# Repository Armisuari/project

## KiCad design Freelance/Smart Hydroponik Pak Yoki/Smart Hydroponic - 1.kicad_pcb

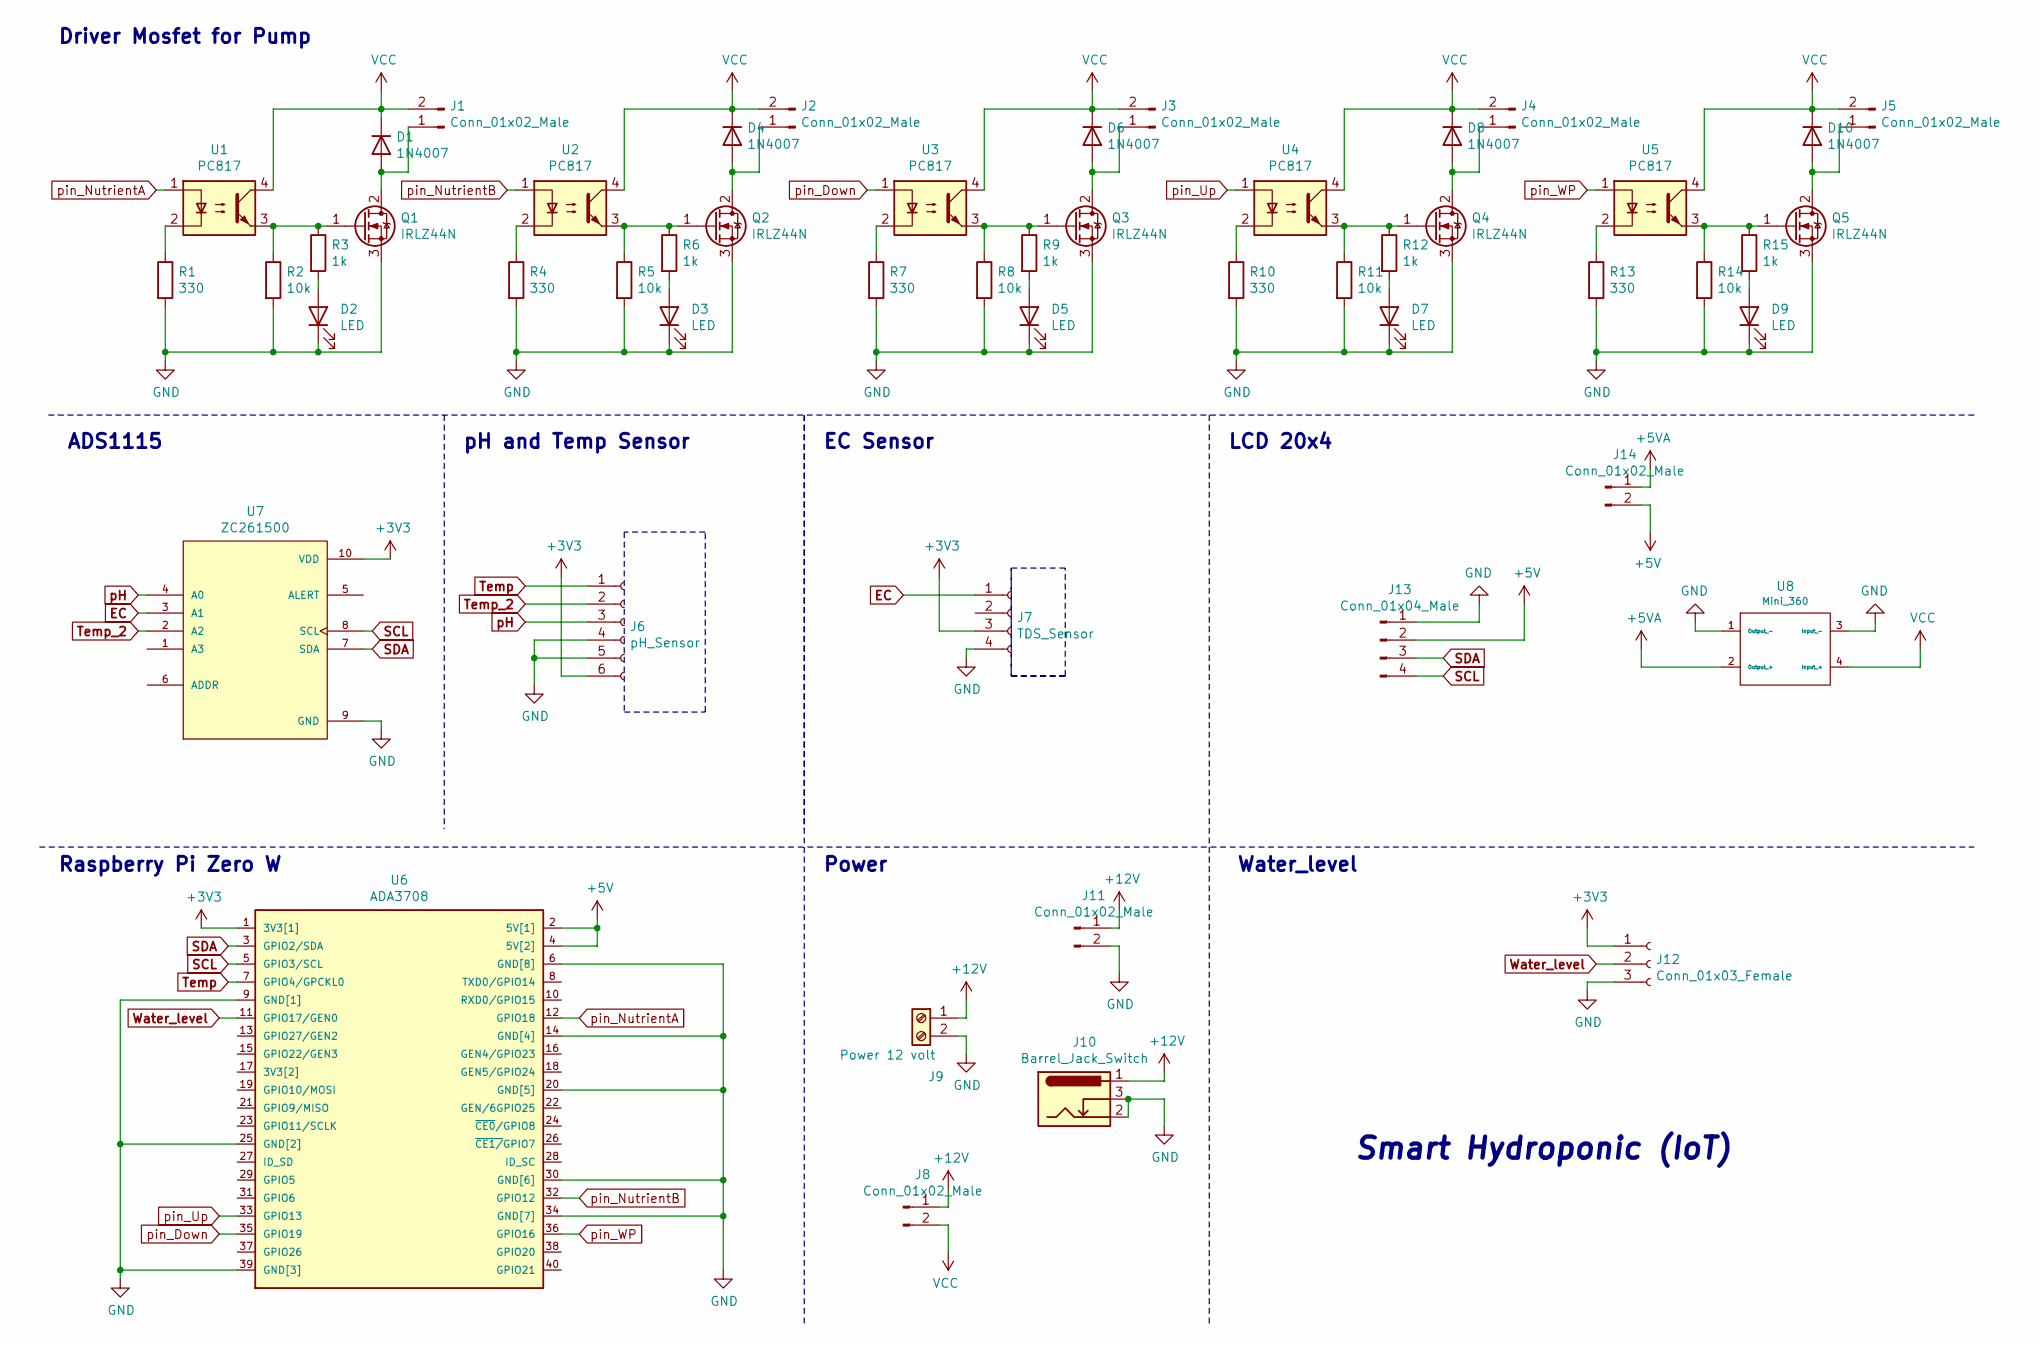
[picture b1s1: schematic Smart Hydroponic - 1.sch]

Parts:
D1, D4, D6, D8, D10: 1N4007; D_DO-41_SOD81_P10.16mm_Horizontal
D2, D3, D5, D7, D9: LED; LED_D3.0mm
J1, J2, J3, J4, J5: Conn_01x02_Male; TerminalBlock_2edg-2_P5.08mm
J6: pH_Sensor; PinHeader_1x06_P2.54mm_Vertical
J7: TDS_Sensor; PinHeader_1x04_P2.54mm_Vertical
J8, J11, J14: Conn_01x02_Male; JST_EH_B2B-EH-A_1x02_P2.50mm_Vertical
J9: Power 12 volt; TerminalBlock_Phoenix_MKDS-1,5-2-5.08_1x02_P5.08mm_Horizont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
J10: Barrel_Jack_Switch; BarrelJack_CUI_PJ-102AH_Horizontal
J12: Conn_01x03_Female; JST_EH_B3B-EH-A_1x03_P2.50mm_Vertical
J13: Conn_01x04_Male; JST_EH_B4B-EH-A_1x04_P2.50mm_Vertical
Q1, Q2, Q3, Q4, Q5: IRLZ44N; TO-220-3_Vertical
R1, R4, R7, R10, R13: 330; R_Axial_DIN0207_L6.3mm_D2.5mm_P10.16mm_Horizontal
R2, R5, R8, R11, R14: 10k; R_Axial_DIN0207_L6.3mm_D2.5mm_P10.16mm_Horizontal
R3, R6, R9, R12, R15: 1k; R_Axial_DIN0207_L6.3mm_D2.5mm_P10.16mm_Horizontal
U1, U2, U3, U4, U5: PC817; DIP-4_W7.62mm
U6: ADA3708; Raspberry_Pi_Zero_Socketed_THT_FaceDown_MountingHoles
U7: ZC261500; MODULE_ZC261500
U8: Mini_360; Mini_360_MP2307

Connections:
+3V3: J6.6, J7.3, J12.1, U6.1 (3V3[1]), U7.10 (VDD)
+5V: J13.2, J14.2, U6.2 (5V[1]), U6.4 (5V[2])
+5VA: J14.1, U8.2 (Output_+)
+12V: J8.1, J9.1, J10.1, J11.1
EC: J7.1, U7.3 (A1)
GND: D2.1 (K), D3.1 (K), D5.1 (K), D7.1 (K), D9.1 (K), J6.4, J6.5, J7.4, J9.2, J10.2, J10.3, J11.2, J12.3, J13.1, Q1.3 (S), Q2.3 (S), Q3.3 (S), Q4.3 (S), Q5.3 (S), R1.2, R2.2, R4.2, R5.2, R7.2, R8.2, R10.2, R11.2, R13.2, R14.2, U6.6 (GND[8]), U6.9 (GND[1]), U6.14 (GND[4]), U6.20 (GND[5]), U6.25 (GND[2]), U6.30 (GND[6]), U6.34 (GND[7]), U6.39 (GND[3]), U7.9 (GND), U8.1 (Output_-), U8.3 (Input_-); also elsewhere on the board
unnamed: D1.2 (A), J1.1, Q1.2 (D)
unnamed 7: D2.2 (A), R3.2; also elsewhere on the board
unnamed 8: D3.2 (A), R6.2; also elsewhere on the board
unnamed: D4.2 (A), J2.1, Q2.2 (D)
unnamed 10: D5.2 (A), R9.2; also elsewhere on the board
unnamed: D6.2 (A), J3.1, Q3.2 (D)
unnamed 12: D7.2 (A), R12.2; also elsewhere on the board
unnamed: D8.2 (A), J4.1, Q4.2 (D)
unnamed 14: D9.2 (A), R15.2; also elsewhere on the board
unnamed: D10.2 (A), J5.1, Q5.2 (D)
unnamed: Q1.1 (G), R2.1, R3.1, U1.3
unnamed: Q2.1 (G), R5.1, R6.1, U2.3
unnamed: Q3.1 (G), R8.1, R9.1, U3.3
unnamed: Q4.1 (G), R11.1, R12.1, U4.3
unnamed: Q5.1 (G), R14.1, R15.1, U5.3
unnamed: R1.1, U1.2
unnamed: R4.1, U2.2
unnamed: R7.1, U3.2
unnamed: R10.1, U4.2
unnamed: R13.1, U5.2
SCL: J13.4, U6.5 (GPIO3/SCL), U7.8 (SCL)
SDA: J13.3, U6.3 (GPIO2/SDA), U7.7 (SDA)
Temp: J6.1, U6.7 (GPIO4/GPCKL0)
Temp_2: J6.2, U7.2 (A2)
VCC: D1.1 (K), D4.1 (K), D6.1 (K), D8.1 (K), D10.1 (K), J1.2, J2.2, J3.2, J4.2, J5.2, J8.2, U1.4, U2.4, U3.4, U4.4, U5.4, U8.4 (Input_+)
Water_level: J12.2, U6.11 (GPIO17/GEN0)
pH: J6.3, U7.4 (A0)
pin_Down: U3.1, U6.35 (GPIO19)
pin_NutrientA: U1.1, U6.12 (GPIO18)
pin_NutrientB: U2.1, U6.32 (GPIO12)
pin_Up: U4.1, U6.33 (GPIO13)
pin_WP: U5.1, U6.36 (GPIO16)

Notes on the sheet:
Raspberry Pi Zero W
LCD 20x4
ADS1115
pH and Temp Sensor
EC Sensor
Power
Driver Mosfet for Pump
Water_level
Smart Hydroponic (IoT)

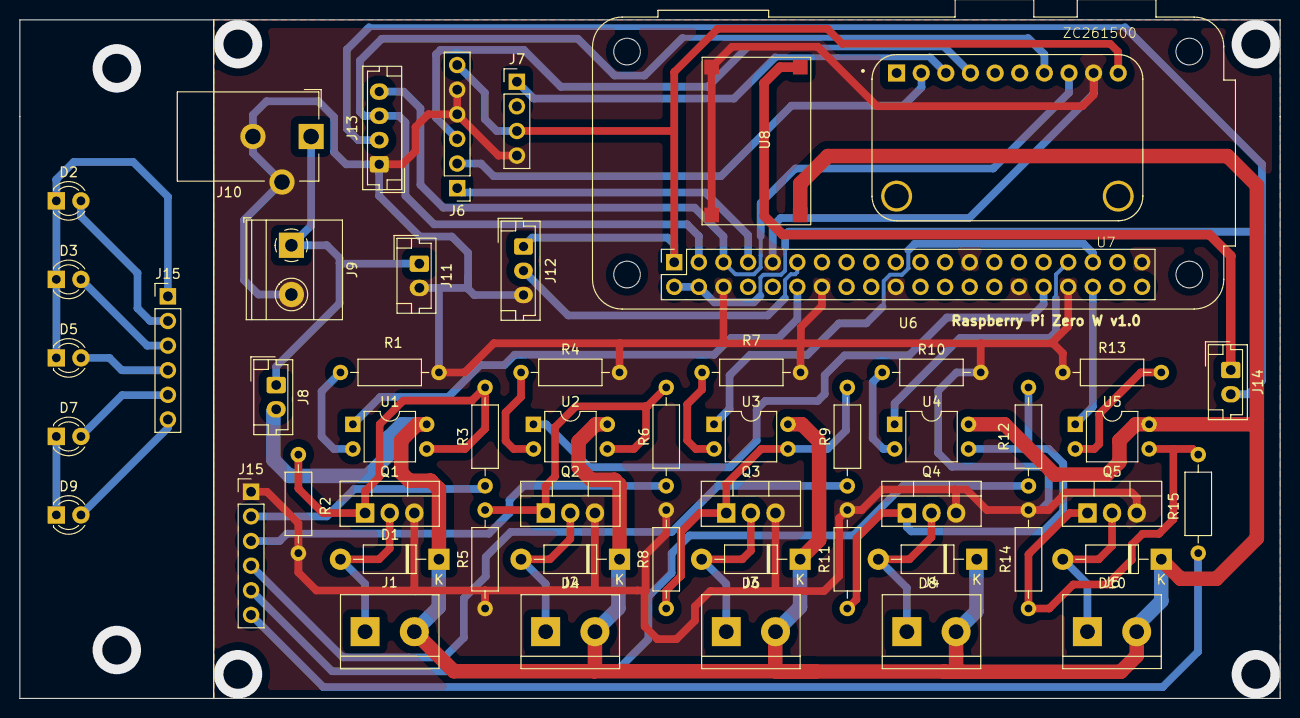
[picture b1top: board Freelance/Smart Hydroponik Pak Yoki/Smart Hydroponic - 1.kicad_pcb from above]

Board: 2 copper layers, 130.0 x 70.0 mm, 54 parts (0 on the bottom side), 38 nets.

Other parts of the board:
J15, J15#2: PinHeader_1x06_P2.54mm_Vertical

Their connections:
GND: J15.1, J15#2.1; also elsewhere on the board
unnamed 7: J15.2, J15#2.2; also elsewhere on the board
unnamed 8: J15.3, J15#2.3; also elsewhere on the board
unnamed 10: J15.4, J15#2.4; also elsewhere on the board
unnamed 12: J15.5, J15#2.5; also elsewhere on the board
unnamed 14: J15.6, J15#2.6; also elsewhere on the board

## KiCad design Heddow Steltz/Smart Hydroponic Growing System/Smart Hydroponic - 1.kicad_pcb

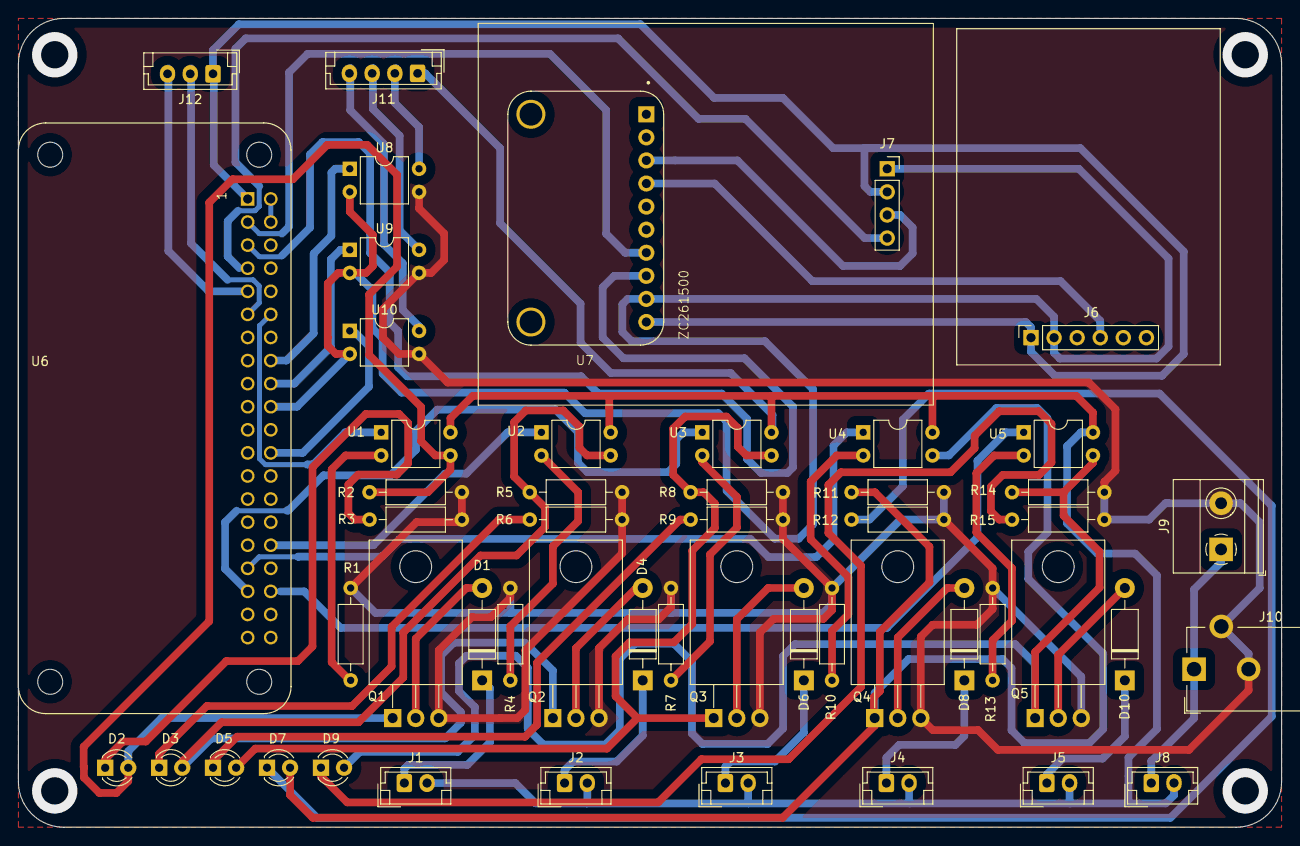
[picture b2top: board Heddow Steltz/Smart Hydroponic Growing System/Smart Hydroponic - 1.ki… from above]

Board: 2 copper layers, 139.0 x 89.0 mm, 52 parts (0 on the bottom side), 48 nets.

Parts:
D1, D4, D6, D8, D10: 1N4007; D_DO-41_SOD81_P10.16mm_Horizontal
D2, D3, D5, D7, D9: LED; LED_D3.0mm
J1, J2, J3, J4, J5, J8: Conn_01x02_Male; JST_EH_B2B-EH-A_1x02_P2.50mm_Vertical
J6: pH_Sensor; PinSocket_1x06_P2.54mm_Vertical
J7: TDS_Sensor; PinSocket_1x04_P2.54mm_Vertical
J9: Power 12 volt; TerminalBlock_Phoenix_MKDS-1,5-2-5.08_1x02_P5.08mm_Horizont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
J10: Barrel_Jack_Switch; BarrelJack_CUI_PJ-102AH_Horizontal
J11: Conn_01x04_Male; JST_EH_B4B-EH-A_1x04_P2.50mm_Vertical
J12: Conn_01x03_Female; JST_EH_B3B-EH-A_1x03_P2.50mm_Vertical
Q1, Q2, Q3, Q4, Q5: IRLZ44N; TO-220-3_Horizontal_TabDown
R1, R4, R7, R10, R13: 330; R_Axial_DIN0207_L6.3mm_D2.5mm_P10.16mm_Horizontal
R2, R5, R8, R11, R14: 10k; R_Axial_DIN0207_L6.3mm_D2.5mm_P10.16mm_Horizontal
R3, R6, R9, R12, R15: 1k; R_Axial_DIN0207_L6.3mm_D2.5mm_P10.16mm_Horizontal
U1, U2, U3, U4, U5, U8, U9, U10: PC817; DIP-4_W7.62mm
U6: ADA3708; ADA3708_RPI-ZERO
U7: ZC261500; MODULE_ZC261500

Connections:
+3V3: J6.1, J7.2, J12.1, U6.1, U7.10
+5V: U6.2, U6.4
+12V: J8.1, J9.1, J10.1
B_LED: U6.24, U10.1
GND: J9.2, J10.2, J10.3, Q1.3, Q2.3, Q3.3, Q4.3, Q5.3, R1.2, R2.2, R3.2, R4.2, R5.2, R6.2, R7.2, R8.2, R9.2, R10.2, R11.2, R12.2, R13.2, R14.2, R15.2, U8.3, U9.3, U10.3
GNDA: J6.2, J7.1, J12.3, U6.6, U6.9, U6.14, U6.20, U6.25, U6.30, U6.34, U6.39, U7.9, U8.2, U9.2, U10.2
G_LED: U6.18, U9.1
unnamed: D1.1, J1.1
unnamed: D1.2, Q1.2
unnamed: D2.1, R3.1
unnamed: D2.2, Q1.1, R2.1, U1.3
unnamed: D3.1, R6.1
unnamed: D3.2, Q2.1, R5.1, U2.3
unnamed: D4.1, J2.1
unnamed: D4.2, Q2.2
unnamed: D5.1, R9.1
unnamed: D5.2, Q3.1, R8.1, U3.3
unnamed: D6.1, J3.1
unnamed: D6.2, Q3.2
unnamed: D7.1, R12.1
unnamed: D7.2, Q4.1, R11.1, U4.3
unnamed: D8.1, J4.1
unnamed: D8.2, Q4.2
unnamed: D9.1, R15.1
unnamed: D9.2, Q5.1, R14.1, U5.3
unnamed: D10.1, J5.1
unnamed: D10.2, Q5.2
unnamed: J11.2, U8.4
unnamed: J11.3, U9.4
unnamed: J11.4, U10.4
unnamed: R1.1, U1.2
unnamed: R4.1, U2.2
unnamed: R7.1, U3.2
unnamed: R10.1, U4.2
unnamed: R13.1, U5.2
R_LED: U6.16, U8.1
SCL: U6.5, U7.8
SDA: U6.3, U7.7
TDS: J7.3, U7.3
Temp: J7.4, U6.7
VCC: J1.2, J2.2, J3.2, J4.2, J5.2, J8.2, J11.1, U1.4, U2.4, U3.4, U4.4, U5.4
Water_level: J12.2, U6.11
pH: J6.4, U7.4
pin_Acid: U1.1, U6.12
pin_Alkaline: U2.1, U6.32
pin_Down: U3.1, U6.35
pin_Up: U4.1, U6.33
pin_WP: U5.1, U6.36

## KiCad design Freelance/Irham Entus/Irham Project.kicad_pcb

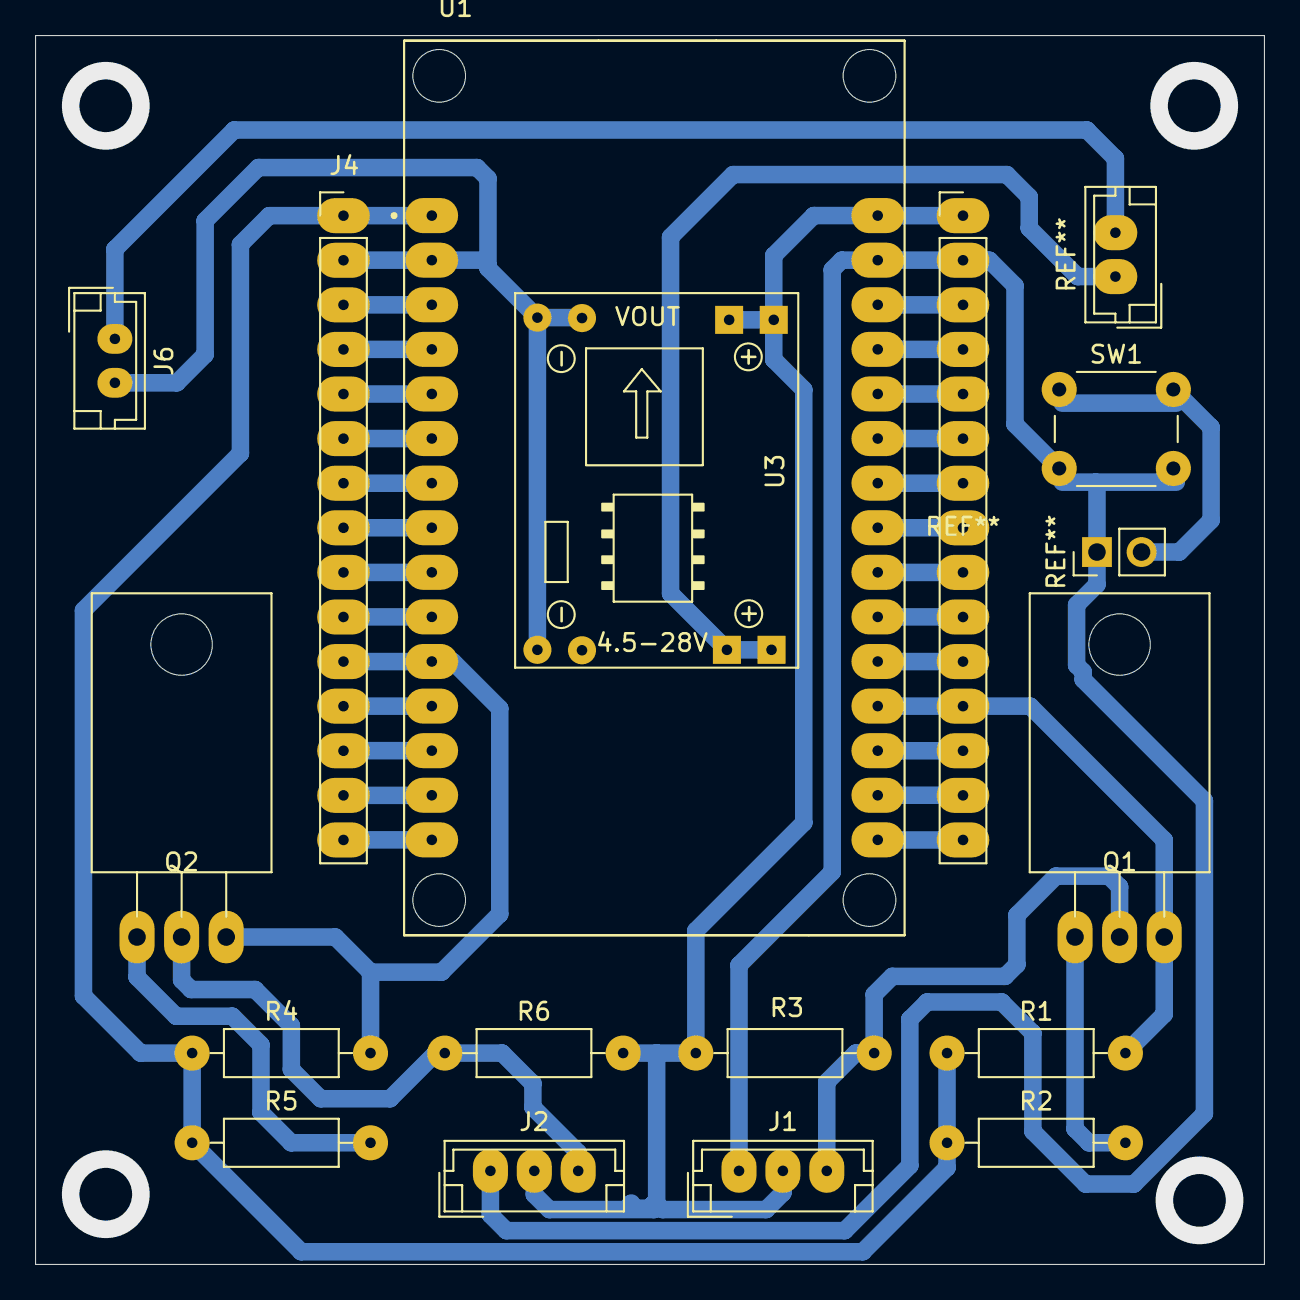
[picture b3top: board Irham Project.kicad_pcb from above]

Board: 2 copper layers, 70.0 x 70.0 mm, 15 parts (0 on the bottom side), 20 nets.

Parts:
J1: Sensor IR_1; JST_EH_B3B-EH-A_1x03_P2.50mm_Vertical
J2: Sensor IR_2; JST_EH_B3B-EH-A_1x03_P2.50mm_Vertical
J4: PinHeader_1x15_P2.54mm_Vertical
J6: JST_EH_B2B-EH-A_1x02_P2.50mm_Vertical
Q1, Q2: TIP41C; TO-220-3_Horizontal_TabDown
R1, R3, R4, R6: 10K; R_Axial_DIN0207_L6.3mm_D2.5mm_P10.16mm_Horizontal
R2, R5: 4.7K; R_Axial_DIN0207_L6.3mm_D2.5mm_P10.16mm_Horizontal
SW1: SW_Push; SW_PUSH_6mm_H7.3mm
U1: ESP32-DEVKIT-V1; MODULE_ESP32_DEVKIT_V1
U3: SRT_Power_3A; SRT_MPT1584EN_Module

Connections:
+3V3: J4.1, R1.1, R2.1, R4.1, R5.1, U1.1
+5V: J1.2, J2.2, R3.2, R6.2, U1.30, U3.3
DC: J4.4, U1.4
GND: J1.1, J2.1, J4.2, J6.2, SW1.2, U1.2, U1.29, U3.2, U3.4
unnamed: J1.3, Q1.2, R3.1
unnamed: J2.3, Q2.2, R6.1
unnamed: Q1.1, R2.2
unnamed: Q2.1, R5.2
unnamed: J4.3, U1.3
unnamed: J4.6, U1.6
unnamed: J4.7, U1.7
unnamed: J4.8, U1.8
unnamed: J4.12, U1.12
unnamed: J4.13, U1.13
unnamed: J4.14, U1.14
RES: J4.5, U1.5
SCL: J4.9, U1.9
SDA: J4.15, U1.15
Sensor_in1: Q1.3, R1.2, U1.19
Sensor_in2: J4.11, Q2.3, R4.2, U1.11

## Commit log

2021-12-13 done add freelance folder with git
2021-12-13 ac auto
2021-12-13 heddow steltz
2022-01-03 Smart Hydroponik Pak Yoki
